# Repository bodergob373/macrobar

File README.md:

# MacroBar
A bar of macro. It has 4 keys, a 2-part case to hold the PCB, a spongey companion, and KMK firmware.
## CAD
Designed in Onshape.

#### Assembly

## Schematic
Designed in KiCad.

## PCB Design
Designed in KiCad.

The XIAO board and two LEDs are on the back.

## BOM
- 4x Cherry MX Switches
- 2x SK6812 MINI Leds
- 1x XIAO RP2040
- 4x Blank DSA Keycaps
- 4x M3x16 Bolt
- 4x M3 Heatset

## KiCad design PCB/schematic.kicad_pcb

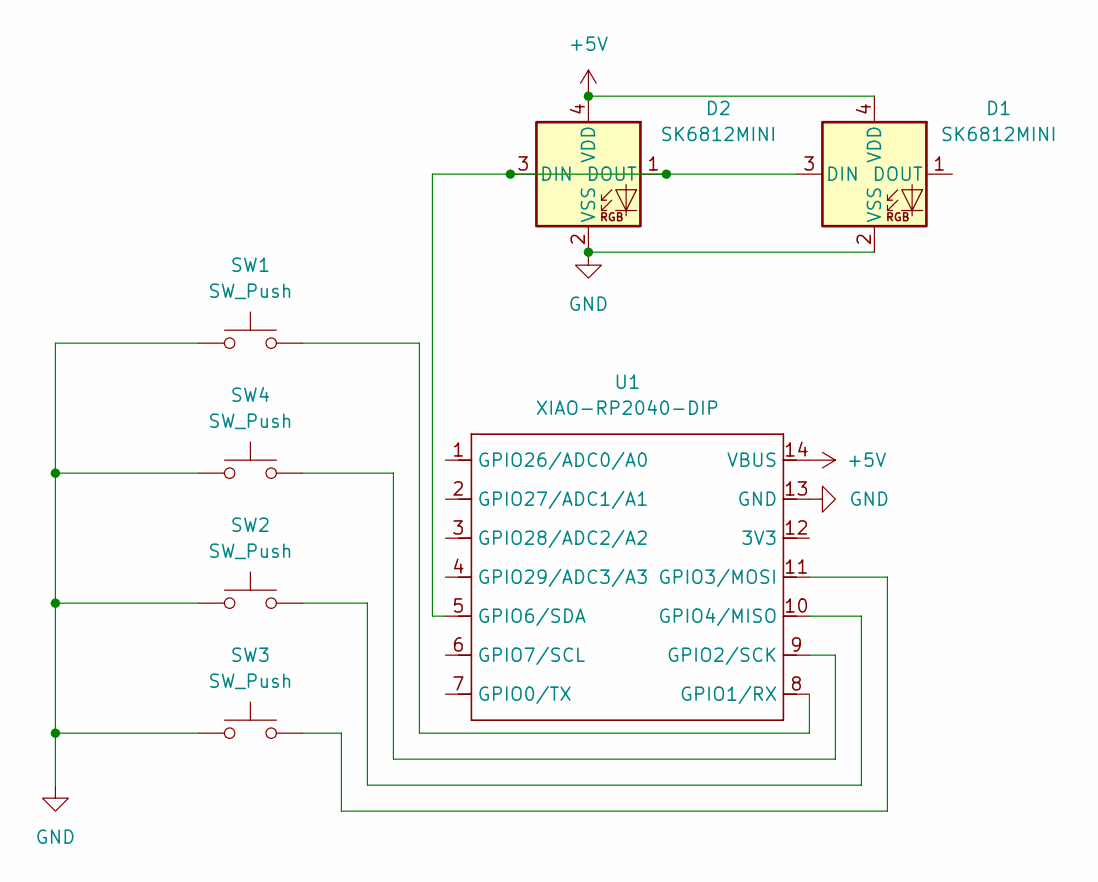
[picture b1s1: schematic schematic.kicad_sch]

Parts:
D1, D2: SK6812MINI; LED_SK6812MINI_PLCC4_3.5x3.5mm_P1.75mm
SW1, SW2, SW3, SW4: SW_Push; SW_Cherry_MX_1.00u_PCB
U1: XIAO-RP2040-DIP

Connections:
+5V: D1.4 (VDD), D2.4 (VDD), U1.14 (VBUS)
GND: D1.2 (VSS), D2.2 (VSS), SW1.1, SW2.1, SW3.1, SW4.1, U1.13 (GND)
unnamed: D1.3 (DIN), D2.1 (DOUT), D2.3 (DIN), U1.5 (GPIO6/SDA)
unnamed: SW1.2, U1.8 (GPIO1/RX)
unnamed: SW4.2, U1.9 (GPIO2/SCK)
unnamed: SW3.2, U1.11 (GPIO3/MOSI)
unnamed: SW2.2, U1.10 (GPIO4/MISO)

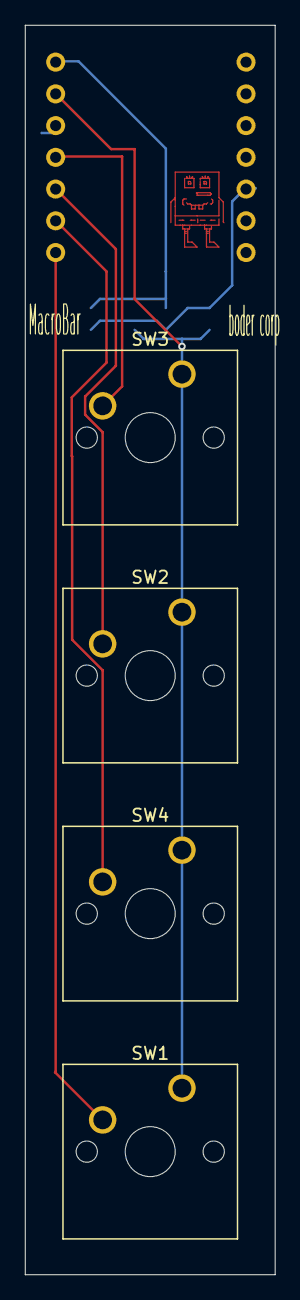
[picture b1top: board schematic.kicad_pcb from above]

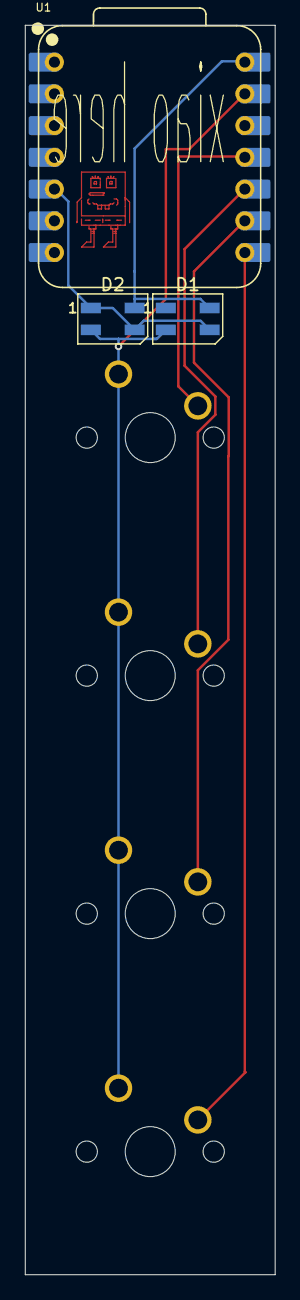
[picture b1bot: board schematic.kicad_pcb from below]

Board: 2 copper layers, 20.0 x 100.0 mm, 7 parts (3 on the bottom side), 7 nets.
